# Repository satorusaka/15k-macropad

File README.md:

# SKMT_15k_Macropad

A diy, 3d-printed, 15 key (3x5), hotswap, RGB macropad.

This repo contains gerber files for PCB, the 3D-printed parts and the QMK firmware for RPi Pico.

[more images](https://imgur.com/a/5BjqMy4)

## Parts Required

- JLCPCB parts:
  - 1x skmt_15k Main Matrix
    - Get stencil to smd solder the components or pay for smd assembly services.
  - 1x skmt_15k Raspberry Pi sub-board
  - 1x USB-C-Breakout board
- SMD parts:
  - 15x 1N4148W SOD-123 Switching Diode
  - 15x sk6812mini-e RGB LED
  - 15x 100nF 0603 Multilayer Ceramic Capacitors
  - 15x kailh hotswap sockets
- THT parts:
  - 1x pin header 1x11p
- Fasterners:
  - 2x M3x12 screws (case)
  - 2x M2.5x4 screws (usb breakout)
  - 4x M2x6 screws (PCB)
- 3D printed parts:
  - 1x Top case
  - 1x Bottom case
  - 1x Plate
  - 4x m2 standoff
- 1x Raspberry Pi Pico
- 15x Keycaps
- 15x Switches

## Assembly Instructions

TO BE ADDED

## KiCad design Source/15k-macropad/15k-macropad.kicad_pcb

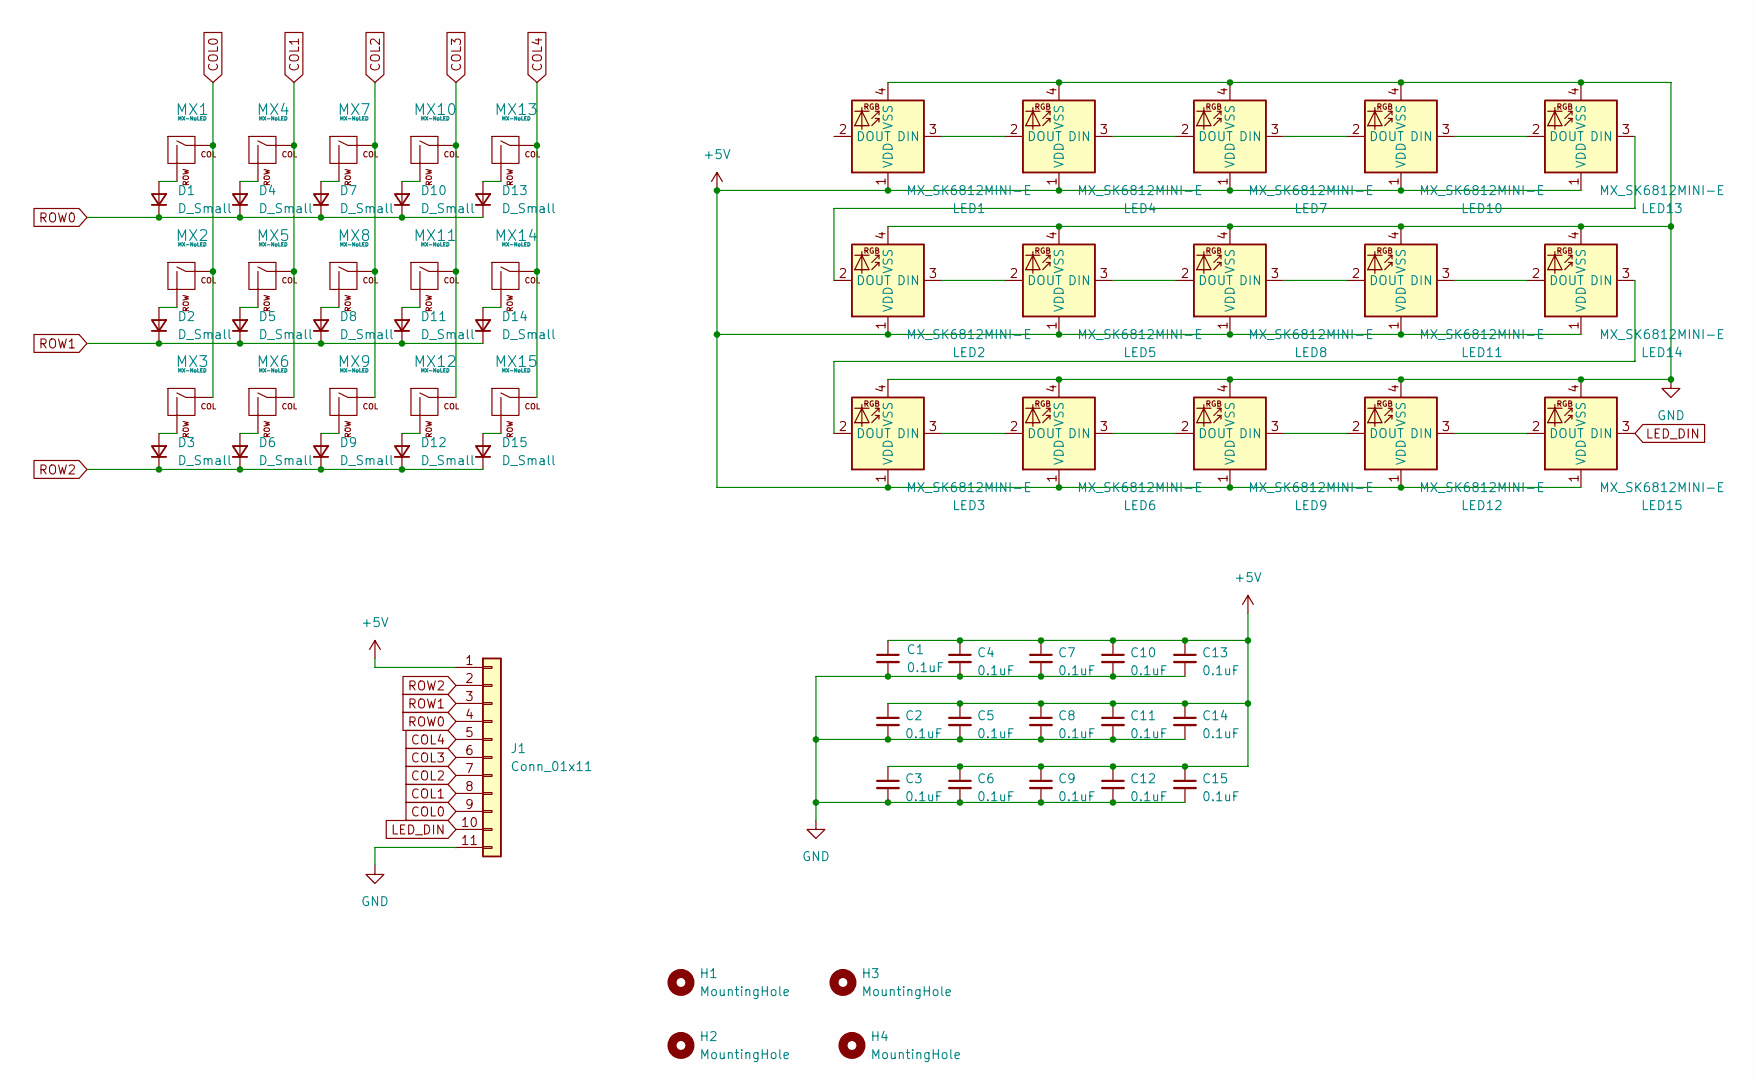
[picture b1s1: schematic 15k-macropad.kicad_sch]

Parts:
C1, C2, C3, C4, C5, C6, C7, C8, C9, C10, C11, C12, C13, C14, C15: 0.1uF; C_0603_1608Metric
D1, D2, D3, D4, D5, D6, D7, D8, D9, D10, D11, D12, D13, D14, D15: D_Small; D_SOD-123
H1, H2, H3, H4: MountingHole; MountingHole_2.2mm_M2
J1: Conn_01x11; PinHeader_1x11_P2.54mm_Vertical
LED1, LED2, LED3, LED4, LED5, LED6, LED7, LED8, LED9, LED10, LED11, LED12, LED13, LED14, LED15: MX_SK6812MINI-E; LED_MX_6028R
MX1, MX2, MX3, MX4, MX5, MX6, MX7, MX8, MX9, MX10, MX11, MX12, MX13, MX14, MX15: MX-NoLED; SW_Hotswap_Kailh_MX_1.00u

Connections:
+5V: C1.1, C2.1, C3.1, C4.1, C5.1, C6.1, C7.1, C8.1, C9.1, C10.1, C11.1, C12.1, C13.1, C14.1, C15.1, J1.1, LED1.1 (VDD), LED2.1 (VDD), LED3.1 (VDD), LED4.1 (VDD), LED5.1 (VDD), LED6.1 (VDD), LED7.1 (VDD), LED8.1 (VDD), LED9.1 (VDD), LED10.1 (VDD), LED11.1 (VDD), LED12.1 (VDD), LED13.1 (VDD), LED14.1 (VDD), LED15.1 (VDD)
COL0: J1.9, MX1.1 (COL), MX2.1 (COL), MX3.1 (COL)
COL1: J1.8, MX4.1 (COL), MX5.1 (COL), MX6.1 (COL)
COL2: J1.7, MX7.1 (COL), MX8.1 (COL), MX9.1 (COL)
COL3: J1.6, MX10.1 (COL), MX11.1 (COL), MX12.1 (COL)
COL4: J1.5, MX13.1 (COL), MX14.1 (COL), MX15.1 (COL)
GND: C1.2, C2.2, C3.2, C4.2, C5.2, C6.2, C7.2, C8.2, C9.2, C10.2, C11.2, C12.2, C13.2, C14.2, C15.2, J1.11, LED1.4 (VSS), LED2.4 (VSS), LED3.4 (VSS), LED4.4 (VSS), LED5.4 (VSS), LED6.4 (VSS), LED7.4 (VSS), LED8.4 (VSS), LED9.4 (VSS), LED10.4 (VSS), LED11.4 (VSS), LED12.4 (VSS), LED13.4 (VSS), LED14.4 (VSS), LED15.4 (VSS)
LED_DIN: J1.10, LED15.3 (DIN)
unnamed: D1.2 (A), MX1.2 (ROW)
unnamed: D2.2 (A), MX2.2 (ROW)
unnamed: D3.2 (A), MX3.2 (ROW)
unnamed: D4.2 (A), MX4.2 (ROW)
unnamed: D5.2 (A), MX5.2 (ROW)
unnamed: D6.2 (A), MX6.2 (ROW)
unnamed: D7.2 (A), MX7.2 (ROW)
unnamed: D8.2 (A), MX8.2 (ROW)
unnamed: D9.2 (A), MX9.2 (ROW)
unnamed: D10.2 (A), MX10.2 (ROW)
unnamed: D11.2 (A), MX11.2 (ROW)
unnamed: D12.2 (A), MX12.2 (ROW)
unnamed: D13.2 (A), MX13.2 (ROW)
unnamed: D14.2 (A), MX14.2 (ROW)
unnamed: D15.2 (A), MX15.2 (ROW)
unnamed: LED1.3 (DIN), LED4.2 (DOUT)
unnamed: LED2.3 (DIN), LED5.2 (DOUT)
unnamed: LED3.3 (DIN), LED6.2 (DOUT)
unnamed: LED4.3 (DIN), LED7.2 (DOUT)
unnamed: LED5.3 (DIN), LED8.2 (DOUT)
unnamed: LED6.3 (DIN), LED9.2 (DOUT)
unnamed: LED7.3 (DIN), LED10.2 (DOUT)
unnamed: LED10.3 (DIN), LED13.2 (DOUT)
unnamed: LED8.3 (DIN), LED11.2 (DOUT)
unnamed: LED11.3 (DIN), LED14.2 (DOUT)
unnamed: LED9.3 (DIN), LED12.2 (DOUT)
unnamed: LED12.3 (DIN), LED15.2 (DOUT)
unnamed: LED2.2 (DOUT), LED13.3 (DIN)
unnamed: LED3.2 (DOUT), LED14.3 (DIN)
ROW0: D1.1 (K), D4.1 (K), D7.1 (K), D10.1 (K), D13.1 (K), J1.4
ROW1: D2.1 (K), D5.1 (K), D8.1 (K), D11.1 (K), D14.1 (K), J1.3
ROW2: D3.1 (K), D6.1 (K), D9.1 (K), D12.1 (K), D15.1 (K), J1.2

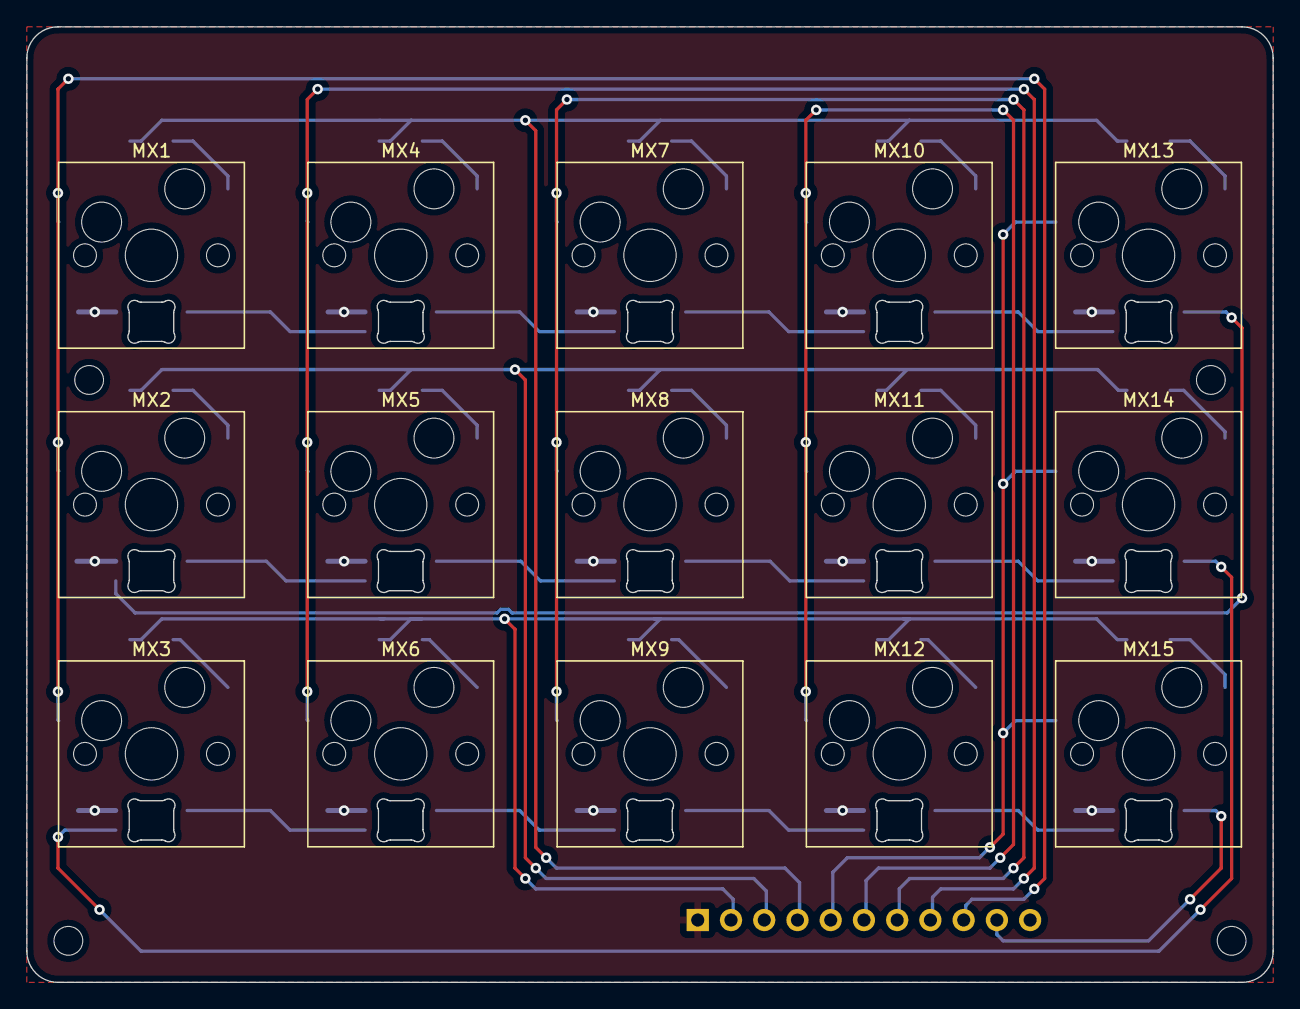
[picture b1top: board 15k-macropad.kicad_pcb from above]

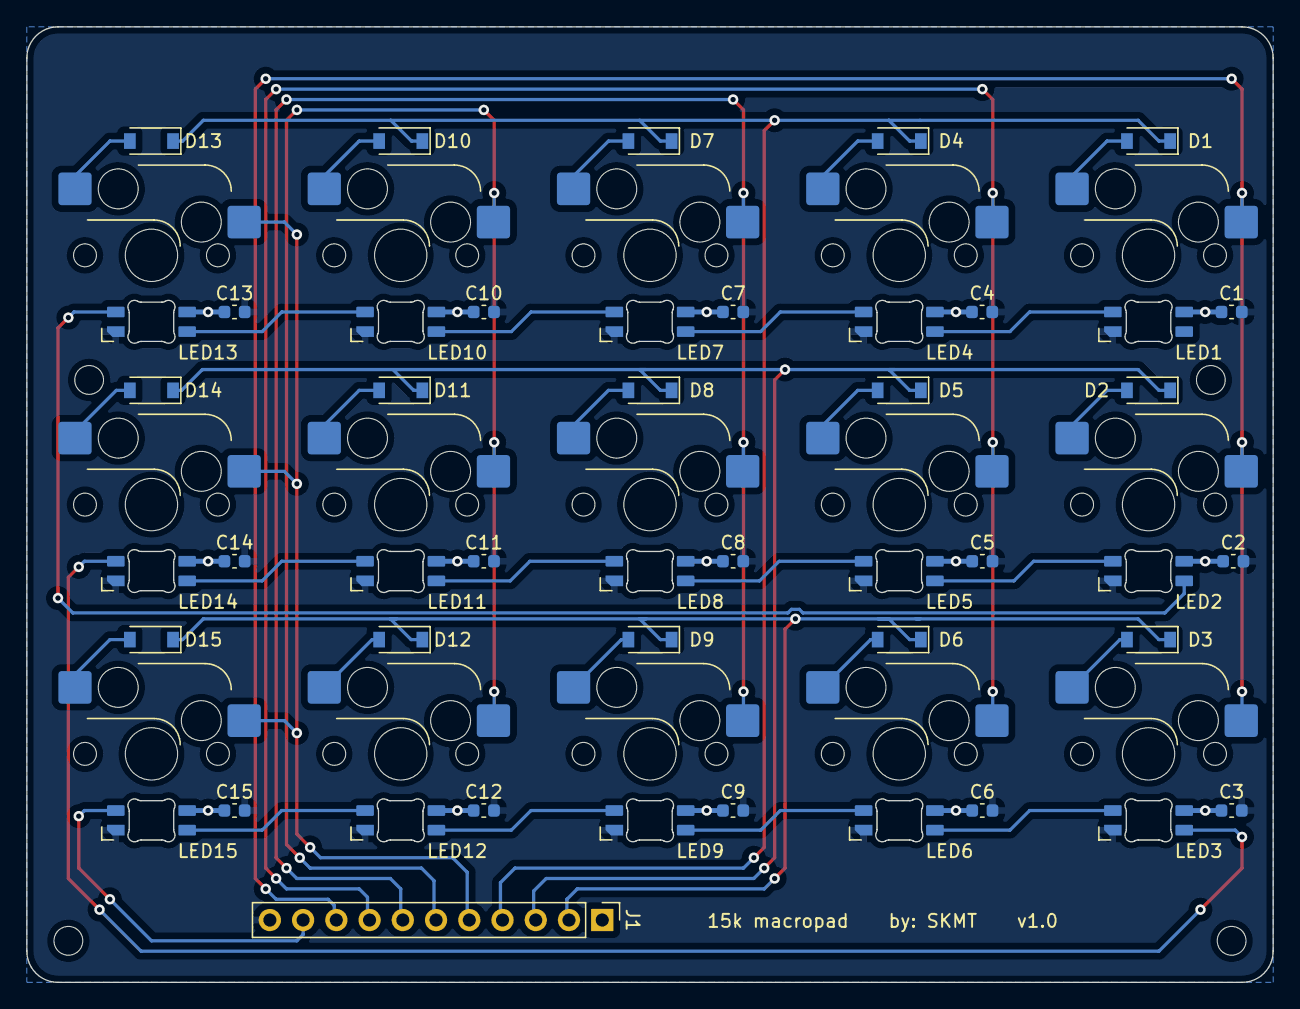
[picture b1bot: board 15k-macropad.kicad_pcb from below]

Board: 2 copper layers, 95.2 x 73.0 mm, 65 parts (46 on the bottom side), 40 nets.

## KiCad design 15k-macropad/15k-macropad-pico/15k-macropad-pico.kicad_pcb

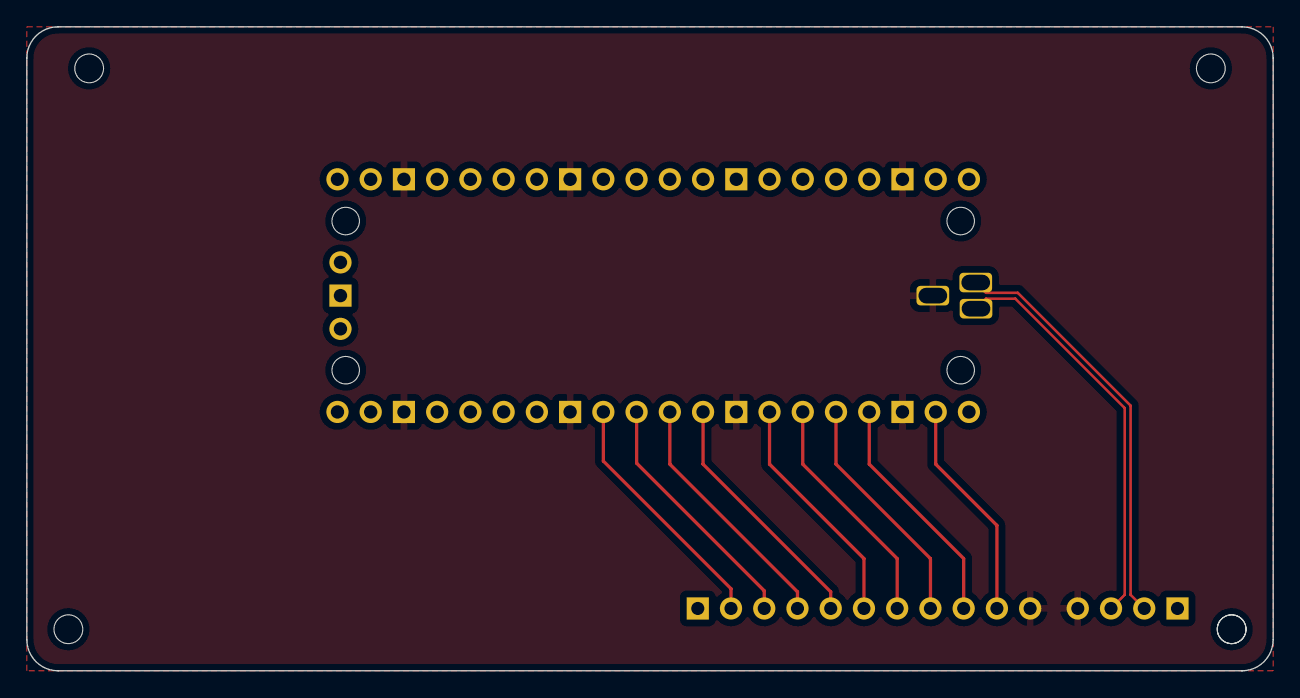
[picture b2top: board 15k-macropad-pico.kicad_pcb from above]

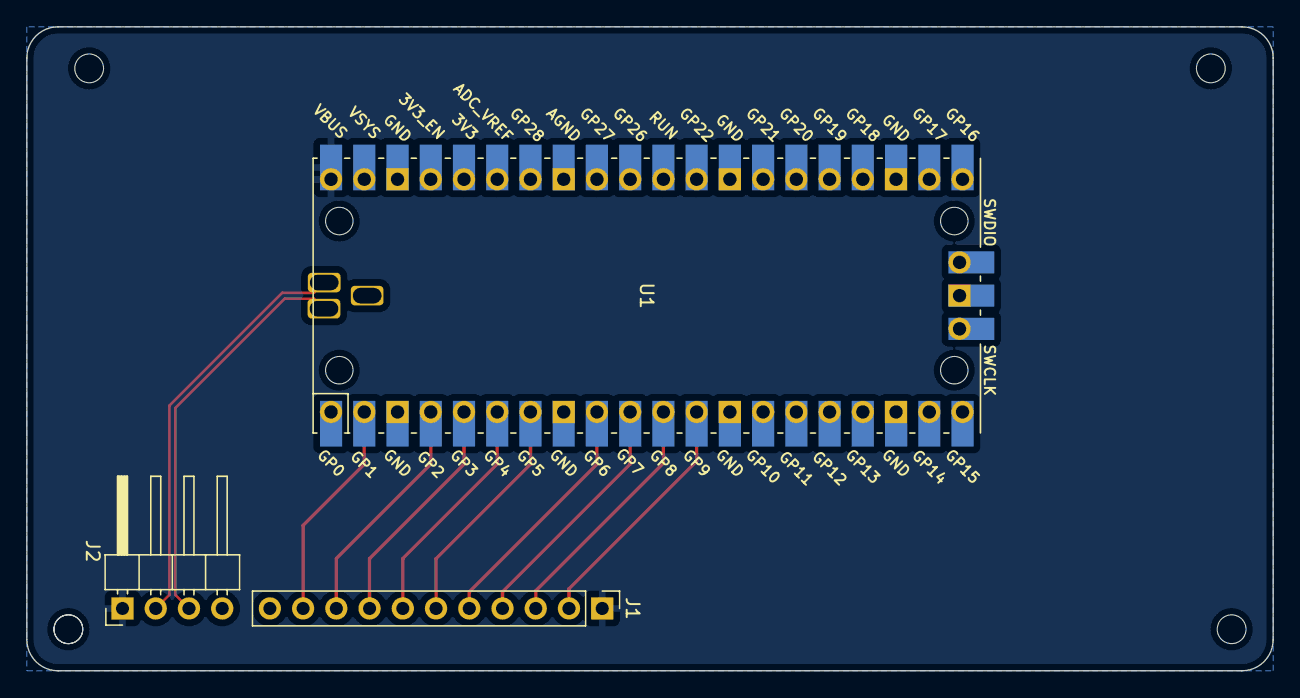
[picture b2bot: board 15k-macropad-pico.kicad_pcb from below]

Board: 2 copper layers, 95.2 x 49.2 mm, 8 parts (3 on the bottom side), 13 nets.

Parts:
H1, H2, H3, H4, H4#2: MountingHole; MountingHole_2.2mm_M2
J1: Conn_01x11; PinHeader_1x11_P2.54mm_Vertical
J2: Conn_01x04; PinHeader_1x04_P2.54mm_Horizontal
U1: Pico; RPi_Pico_SMD_TH

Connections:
+5V: J1.1, J2.1, U1.40 (VBUS)
COL0: J1.9, U1.4 (GPIO2)
COL1: J1.8, U1.5 (GPIO3)
COL2: J1.7, U1.6 (GPIO4)
COL3: J1.6, U1.7 (GPIO5)
COL4: J1.5, U1.9 (GPIO6)
D+: J2.3, U1.TP3
D-: J2.2, U1.TP2
GND: J1.11, J2.4, U1.3 (GND), U1.8 (GND), U1.13 (GND), U1.18 (GND), U1.23 (GND), U1.28 (GND), U1.38 (GND), U1.TP1
LED_DIN: J1.10, U1.2 (GPIO1)
ROW0: J1.4, U1.10 (GPIO7)
ROW1: J1.3, U1.11 (GPIO8)
ROW2: J1.2, U1.12 (GPIO9)

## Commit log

2022-08-13 init
2022-08-13 Add submodules
2022-08-13 added libs
2022-09-09 moved files
2022-09-09 update readme and added firmware
2022-09-09 renamed firmware
